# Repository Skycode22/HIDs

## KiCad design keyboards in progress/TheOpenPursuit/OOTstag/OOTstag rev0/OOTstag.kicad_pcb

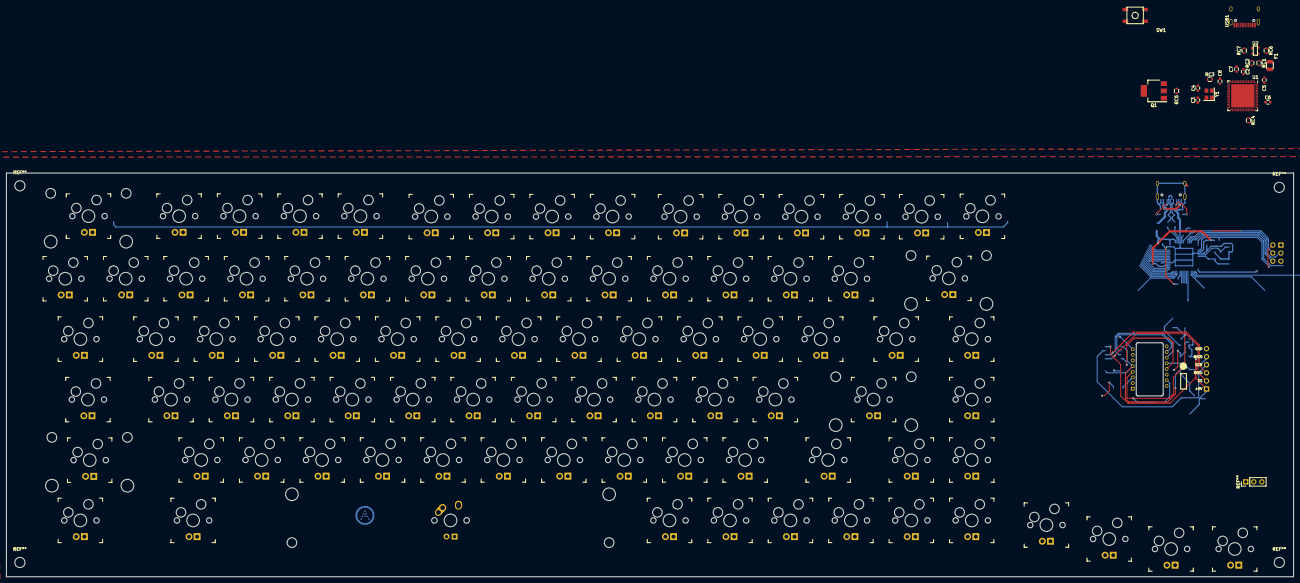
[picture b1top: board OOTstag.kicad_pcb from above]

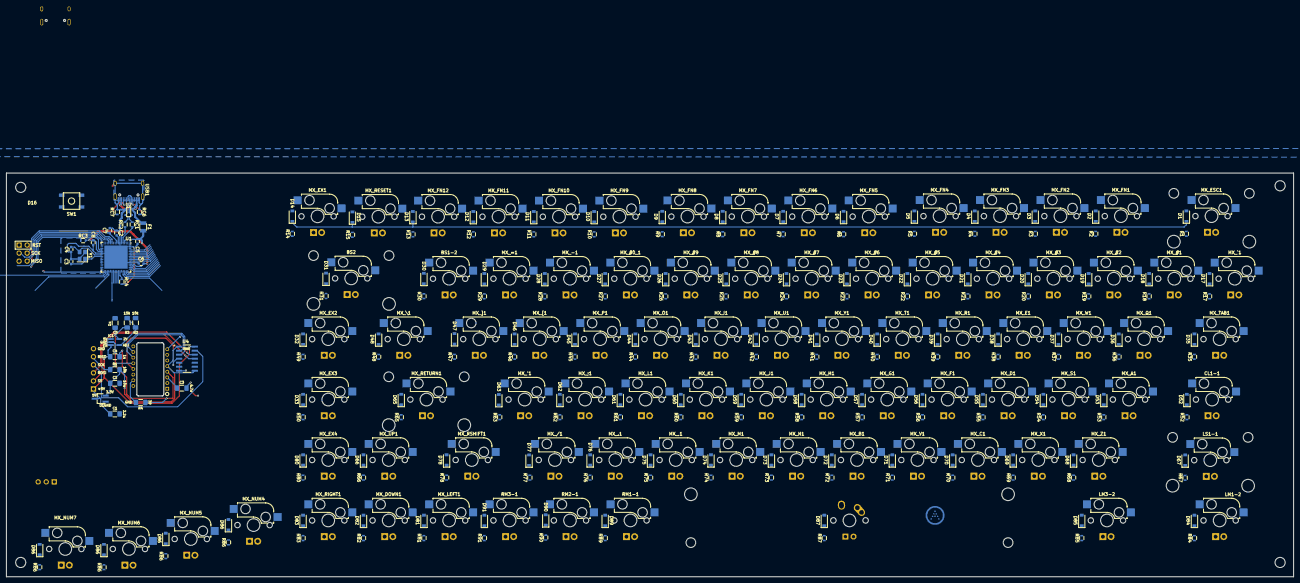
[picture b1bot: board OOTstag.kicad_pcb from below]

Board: 2 copper layers, 405.8 x 127.2 mm, 313 parts (205 on the bottom side), 14 nets.

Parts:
BS1-2: Kailh_socket_MX_led
BS2: Kailh_socket_MX_led stab
C1: 2.2uF; C_1206_3216Metric_Pad1.42x1.75mm_HandSolder
C2, C2#2, C5, C5#2: 1uF; C_0603
C2#3: 10uF; C_1206_3216Metric_Pad1.42x1.75mm_HandSolder
C3, C3#3, C4, C4#2: 22pF; C_0603
C3#2: 4.7uF; C_1206_3216Metric_Pad1.42x1.75mm_HandSolder
C4#3, C5#3: 1uF; C_1206_3216Metric_Pad1.42x1.75mm_HandSolder
C6, C6#2, C7, C7#2, C8, C8#2: 0.1uF; C_0603
CL1-1: Kailh_socket_MX_led
D1, D2, D3, D4, D5, D6, D7, D8, D9, D10, D11, D12, D13, D14, D15, D17, D18, D19, D20, D21, D22, D23, D24, D25, D26, D27, D28, D29, D30, D31, D32, D33, D35, D36, D37, D38, D39, D40, D41, D42, D43, D44, D45, D46, D47, D48, D52, D53, D54, D55, D56, D57, D58, D59, D60, D61, D62, D63, D65, D66, D67, D68, D69, D70, D71, D72, D73, D74, D75, D76, D77, D78, D80, D81, D82, D83, D84, D85, D86, D86#2, D86#3, D86#4, D87, D89, D90, D91: SOD-323; D_SOD-123
F1, F1#2: 500mA; Fuse_SMD1206_Reflow
IC1: AP7335-WG-7; AP7331
J1: Conn_01x06_Female; PinHeader_1x06_P2.54mm_Vertical
J1#2: AVR-ISP-6; Reset_Pretty-Mask
LM1-2: MX-1.5U; Kailh_socket_MX_led
LM3-2: Kailh_socket_MX_led
LS1-1: Kailh_socket_MX_led stab
MX_#0_1, MX_#1, MX_#2, MX_#3, MX_#4, MX_#5, MX_#6, MX_#7, MX_#8, MX_#9: Kailh_socket_MX_led
MX_'1: Kailh_socket_MX_led
MX_,1: Kailh_socket_MX_led
MX_-1: Kailh_socket_MX_led
MX_.1: Kailh_socket_MX_led
MX_/1: Kailh_socket_MX_led
MX_;1: Kailh_socket_MX_led
MX_=1: Kailh_socket_MX_led
MX_A1: Kailh_socket_MX_led
MX_B1: Kailh_socket_MX_led
MX_C1: Kailh_socket_MX_led
MX_D1: Kailh_socket_MX_led
MX_DOWN1: Kailh_socket_MX_led
MX_E1: Kailh_socket_MX_led
MX_ESC1: Kailh_socket_MX_led stab
MX_EX1, MX_EX2, MX_EX3, MX_EX4: Kailh_socket_MX_led
MX_F1: Kailh_socket_MX_led
MX_FN1, MX_FN2, MX_FN3, MX_FN4, MX_FN5, MX_FN6, MX_FN7, MX_FN8, MX_FN9, MX_FN10, MX_FN11, MX_FN12: Kailh_socket_MX_led
MX_G1: Kailh_socket_MX_led
MX_H1: Kailh_socket_MX_led
MX_I1: Kailh_socket_MX_led
MX_J1: Kailh_socket_MX_led
MX_K1: Kailh_socket_MX_led
MX_L1: Kailh_socket_MX_led
MX_LEFT1: Kailh_socket_MX_led
MX_M1: Kailh_socket_MX_led
MX_N1: Kailh_socket_MX_led
MX_NUM4, MX_NUM5, MX_NUM6, MX_NUM7: Kailh_socket_MX_led
MX_O1: Kailh_socket_MX_led
MX_P1: Kailh_socket_MX_led
MX_Q1: Kailh_socket_MX_led
MX_R1: Kailh_socket_MX_led
MX_RESET1: Kailh_socket_MX_led
MX_RETURN1: Kailh_socket_MX_led stab
MX_RIGHT1: Kailh_socket_MX_led
MX_RSHIFT1: Kailh_socket_MX_led
MX_S1: Kailh_socket_MX_led
MX_T1: Kailh_socket_MX_led
MX_TAB1: Kailh_socket_MX_led
MX_U1: Kailh_socket_MX_led
MX_UP1: Kailh_socket_MX_led
MX_V1: Kailh_socket_MX_led
MX_W1: Kailh_socket_MX_led
MX_X1: Kailh_socket_MX_led
MX_Y1: Kailh_socket_MX_led
MX_Z1: Kailh_socket_MX_led
MX_[1: Kailh_socket_MX_led
MX_\1: Kailh_socket_MX_led
MX_]1: Kailh_socket_MX_led
MX_`1: Kailh_socket_MX_led
Q1: DSS60601MZ4-13; SOT-223-3_TabPin2
R1, R2#2: 10k; R_1206_3216Metric_Pad1.42x1.75mm_HandSolder
R1#2, R2, R3, R4, R5, R6, R7, R8, R9, R10, R11, R12, R13, R14, R15, R17, R18, R19, R20, R21, R22, R23, R24, R25, R26, R27, R28, R29, R30, R31, R35, R36, R37, R38, R39, R40, R41, R42, R43, R44, R45, R46, R47, R48, R49, R50, R52, R53, R54, R55, R56, R57, R58, R59, R60, R61, R62, R63, R65, R66, R67, R68, R69, R70, R71, R72, R73, R74, R75, R76, R77, R78, R80, R81, R82, R83, R84, R85, R86, R86#2, R86#3, R86#4, R87, R89, R90, R91: 1k; R_0603
R3#2: 15k; R_1206_3216Metric_Pad1.42x1.75mm_HandSolder
R4#2: 39; R_1206_3216Metric_Pad1.42x1.75mm_HandSolder
RC1, RC1#2, RC2, RC2#2: 22; R_0603
RC3, RC3#2: 10k; R_0603
RC4, RC4#2: 1k; R_0603
RC5: 1.5k; R_0603
RC6, RC6#2, RC7, RC7#2: 5k1; R_0603
RM1-1, RM2-1, RM3-1: Kailh_socket_MX_led
SP1: MX-6.25U; MX-6.25U-ReversedStabilizers
SW1, SW1#2: SW_Push; SKQG-1155865
U1, U1#3: AT90USB1286-AU; QFN-64-1EP_9x9mm_Pitch0.5mm
U1#2: XC6206P332MR; TSOT-23_HandSoldering
U2, U2#3: PRTR5V0U2X; SOT143B
U2#2: PMW3360DM-T2QU; DIP-16_W10.16mm
U4: TXS0104EDR; SOIC127P600X175-14N
USB1, USB1#2: HRO-TYPE-C-31-M-12; HRO-TYPE-C-31-M-12-Assembly
Y1, Y1#2: 16MHz; Crystal_SMD_3225-4pin_3.2x2.5mm

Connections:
GND: C1.2, C2#2.2, C2#3.2, C3#2.2, C3#3.2, C4#2.2, C4#3.2, C5#2.1, C5#3.2, C6#2.1, C7#2.1, C8#2.1, IC1.2 (GND), J1.1, J1#2.6, R2#2.2, RC4#2.2, RC6#2.1, RC7#2.1, SW1#2.1, U1#2.1 (GND), U1#3.6, U1#3.22, U1#3.53, U1#3.63, U1#3.65, U2#2.8 (GND), U2#3.1, U4.7 (GND), USB1#2.1, USB1#2.12, USB1#2.13, Y1#2.2, Y1#2.4
MISO: J1.2, J1#2.1, R1.2, U1#3.13, U2#2.12 (MISO)
MOSI: J1#2.4, U1#3.12, U2#2.11 (MOSI), U4.3 (A2)
MOSI_I: J1.4, U4.12 (B2)
NCS: U2#2.13 (NCS), U4.4 (A3)
NCS_I: J1.5, U4.11 (B3)
unnamed: C3#2.1, U2#2.3 (VDDPIX)
unnamed: IC1.4 (ADJ), R2#2.1, R3#2.1
unnamed: R4#2.2, U2#2.15 (LED_P)
SCLK: U2#2.10 (SCLK), U4.2 (A1)
SCLK_I: J1.3, U4.13 (B1)
VDD_2V: C5#3.1, IC1.5 (OUT), R3#2.2, R4#2.1, U2#2.4 (VDD)
VDD_3.3V: C2#3.1, R1.1, U1#2.2 (VO), U2#2.5 (VDDIO), U4.1 (VCCA), U4.8 (OE)
VDD_5V: C1.1, C4#3.1, IC1.1 (IN), IC1.3 (EN), J1.6, U1#2.3 (VI), U4.14 (VCCB)
